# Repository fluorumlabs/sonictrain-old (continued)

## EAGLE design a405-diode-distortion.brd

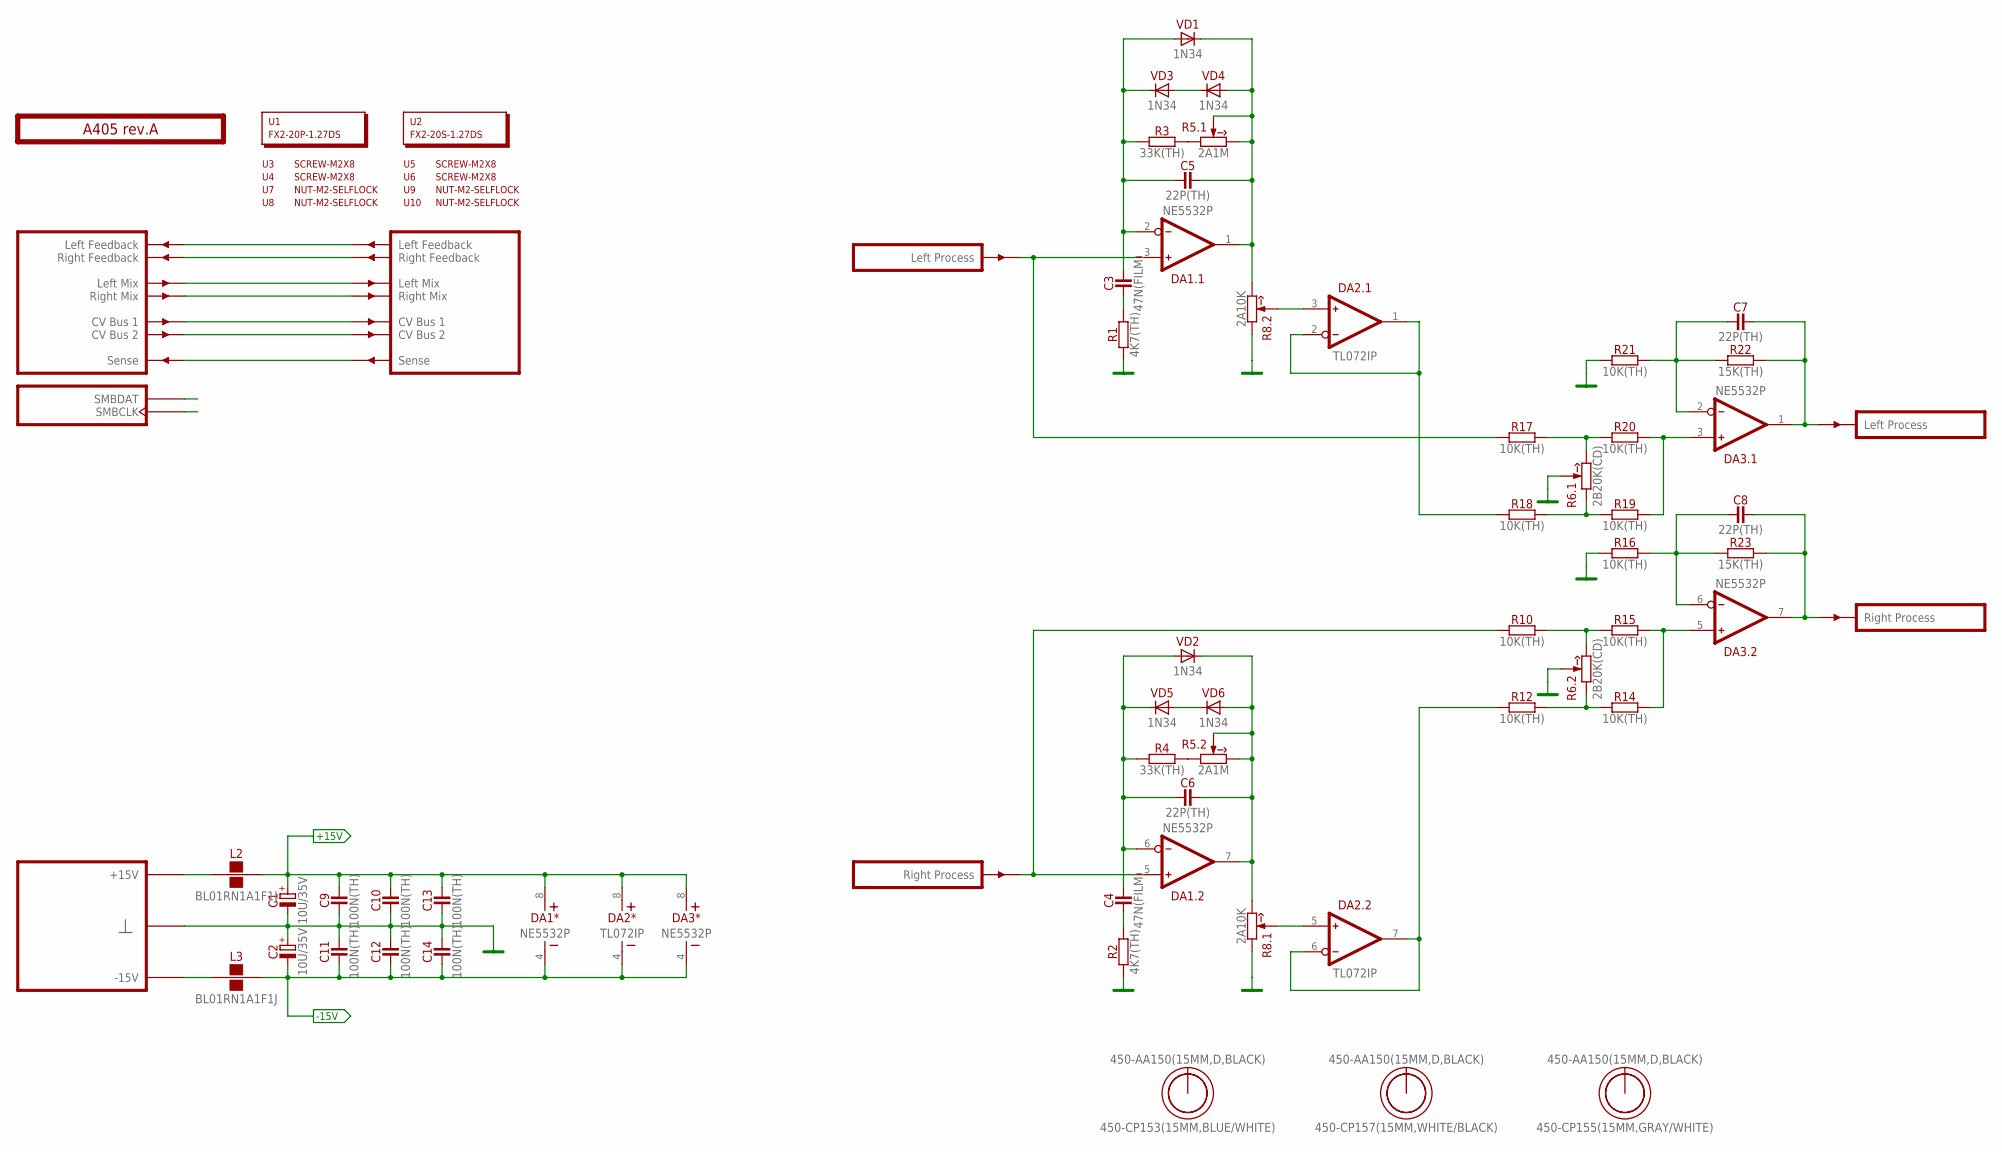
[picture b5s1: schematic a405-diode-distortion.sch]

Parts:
C1, C2: 10U/35V; E2-5
C3, C4: 47N(FILM); C050-025X075
C5, C6, C7, C8: 22P(TH); C050-024X044
C9, C10, C11, C12, C13, C14: 100N(TH); C050-024X044
DA1, DA3: NE5532P; DIP-8
DA2: TL072IP; DIP-8
L2, L3: BL01RN1A1F1J; BL01RN1A
O2, O3, O4: 450-AA150(15MM,D,BLACK); EMPTY
O5: 450-CP155(15MM,GRAY/WHITE); EMPTY
O6: 450-CP157(15MM,WHITE/BLACK); EMPTY
O7: 450-CP153(15MM,BLUE/WHITE); EMPTY
PCB1: A405 rev.A; ST2-BOARD-50
R1, R2: 4K7(TH); R-0207/10
R3, R4: 33K(TH); R-0207/10
R5: 2A1M; RV11-DUAL
R6: 2B20K(CD); RV11-DUAL
R8: 2A10K; RV11-DUAL
R10, R12, R14, R15, R16, R17, R18, R19, R20, R21: 10K(TH); R-0207/10
R22, R23: 15K(TH); R-0207/10
U1: FX2-20P-1.27DS; EMPTY
U2: FX2-20S-1.27DS; EMPTY
U3, U4, U5, U6: SCREW-M2X8; EMPTY
U7, U8, U9, U10: NUT-M2-SELFLOCK; EMPTY
VD1, VD2, VD3, VD4, VD5, VD6: 1N34; DO35-15

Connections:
+15V: C1.+, C9.2, C10.2, C13.2, DA1.8 (V+), DA2.8 (V+), DA3.8 (V+), L2.2
-15V: C2.-, C11.1, C12.1, C14.1, DA1.4 (V-), DA2.4 (V-), DA3.4 (V-), L3.2
FBK_LEFT: PCB1.ALFBK (LFBK), PCB1.ALFBK' (LFBK')
FBK_RIGHT: PCB1.ARFBK (RFBK), PCB1.ARFBK' (RFBK')
GND: C1.-, C2.+, C9.1, C10.1, C11.2, C12.2, C13.1, C14.2, PCB1.B4 (GND), PCB1.B4' (GND), PCB1.B5 (GND), PCB1.B5' (GND), PCB1.B6 (GND), PCB1.B6' (GND), PCB1.B7 (GND), PCB1.B7' (GND), PCB1.B8 (GND), PCB1.B8' (GND), R1.1, R2.1, R6.2 (W), R6.2' (W), R8.1 (CCW), R8.1' (CCW), R16.1, R21.1
LMIX: PCB1.ALMIX (LMIX), PCB1.ALMIX' (LMIX')
unnamed: R3.2, R5.1 (CCW)
unnamed: R4.2, R5.1' (CCW)
unnamed: C7.2, DA3.1 (OUT), PCB1.BOUTL' (OUTL), R22.2
unnamed: C3.1, R1.2
unnamed: R6.3 (CW), R17.2, R20.1
unnamed: DA1.5 (IN+), PCB1.BINR (INR), R10.1
unnamed: C6.2, DA1.7 (OUT), R5.2' (W), R5.3' (CW), R8.3 (CW), VD2.C, VD6.A
unnamed: C4.1, R2.2
unnamed: C5.2, DA1.1 (OUT), R5.2 (W), R5.3 (CW), R8.3' (CW), VD1.C, VD4.A
unnamed: C4.2, C6.1, DA1.6 (IN-), R4.1, VD2.A, VD5.C
unnamed: C8.1, DA3.6 (IN-), R16.2, R23.1
unnamed: DA3.5 (IN+), R14.2, R15.2
unnamed: DA3.3 (IN+), R19.2, R20.2
unnamed: VD3.A, VD4.C
unnamed: R6.1' (CCW), R12.2, R14.1
unnamed: PCB1.BSENSE (SENSE), PCB1.BSENSE' (SENSE')
unnamed: C3.2, C5.1, DA1.2 (IN-), R3.1, VD1.A, VD3.C
unnamed: DA1.3 (IN+), PCB1.BINL (INL), R17.1
unnamed: C8.2, DA3.7 (OUT), PCB1.BOUTR' (OUTR), R23.2
unnamed: VD5.A, VD6.C
unnamed: DA2.5 (IN+), R8.2 (W)
unnamed: DA2.6 (IN-), DA2.7 (OUT), R12.1
unnamed: DA2.3 (IN+), R8.2' (W)
unnamed: DA2.1 (OUT), DA2.2 (IN-), R18.1
unnamed: L3.1, PCB1.A-15 (P-15V), PCB1.A-15' (P-15V), PCB1.B-15 (P-15V), PCB1.B-15' (P-15V)
unnamed: PCB1.ASMBDAT (SMBDAT), PCB1.ASMBDAT' (SMBDAT)
unnamed: PCB1.ACV1 (CV1), PCB1.ACV1' (CV1')
unnamed: PCB1.ACV2 (CV2), PCB1.ACV2' (CV2')
unnamed: PCB1.ASMBCLK (SMBCLK), PCB1.ASMBCLK' (SMBCLK)
unnamed: R6.1 (CCW), R18.2, R19.1
unnamed: R6.3' (CW), R10.2, R15.1
unnamed: C7.1, DA3.2 (IN-), R21.2, R22.1
P+15V: L2.1, PCB1.A+15 (P+15V), PCB1.A+15' (P+15V), PCB1.B+15 (P+15V), PCB1.B+15' (P+15V)
RMIX: PCB1.ARMIX (RMIX), PCB1.ARMIX' (RMIX')

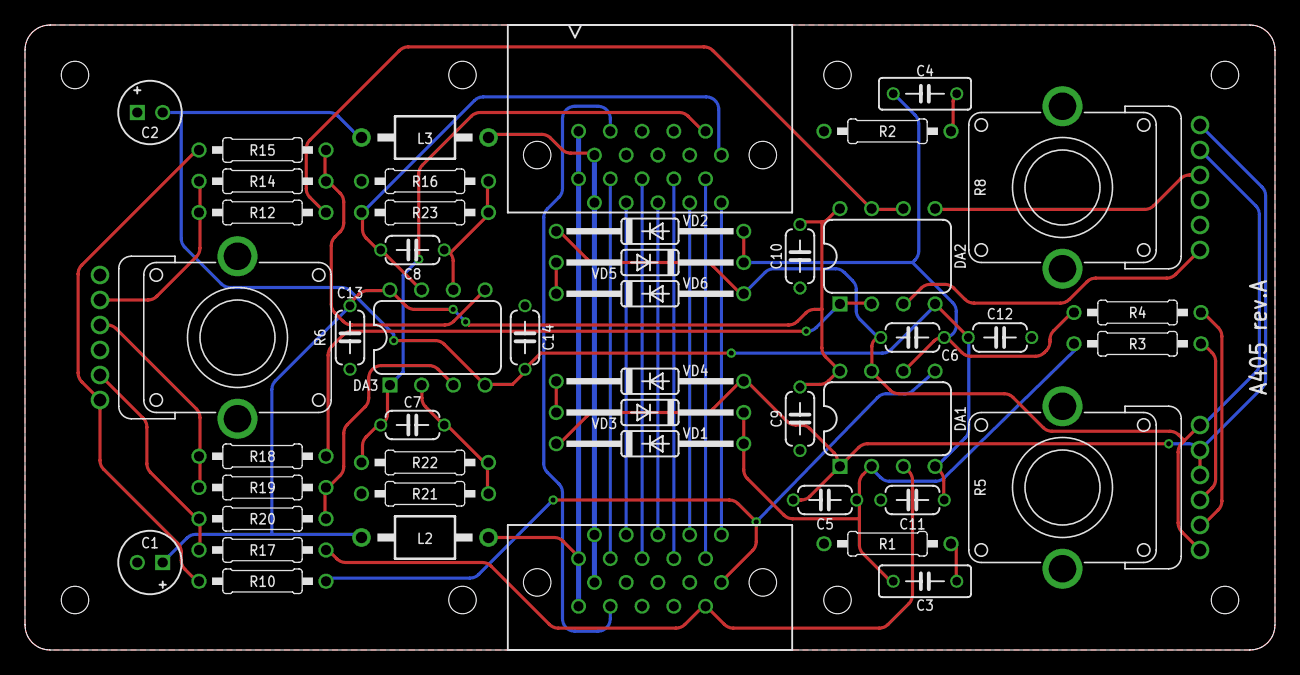
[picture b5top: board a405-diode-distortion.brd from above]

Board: 2 copper layers, 100.0 x 50.0 mm, 61 parts (0 on the bottom side), 40 nets.

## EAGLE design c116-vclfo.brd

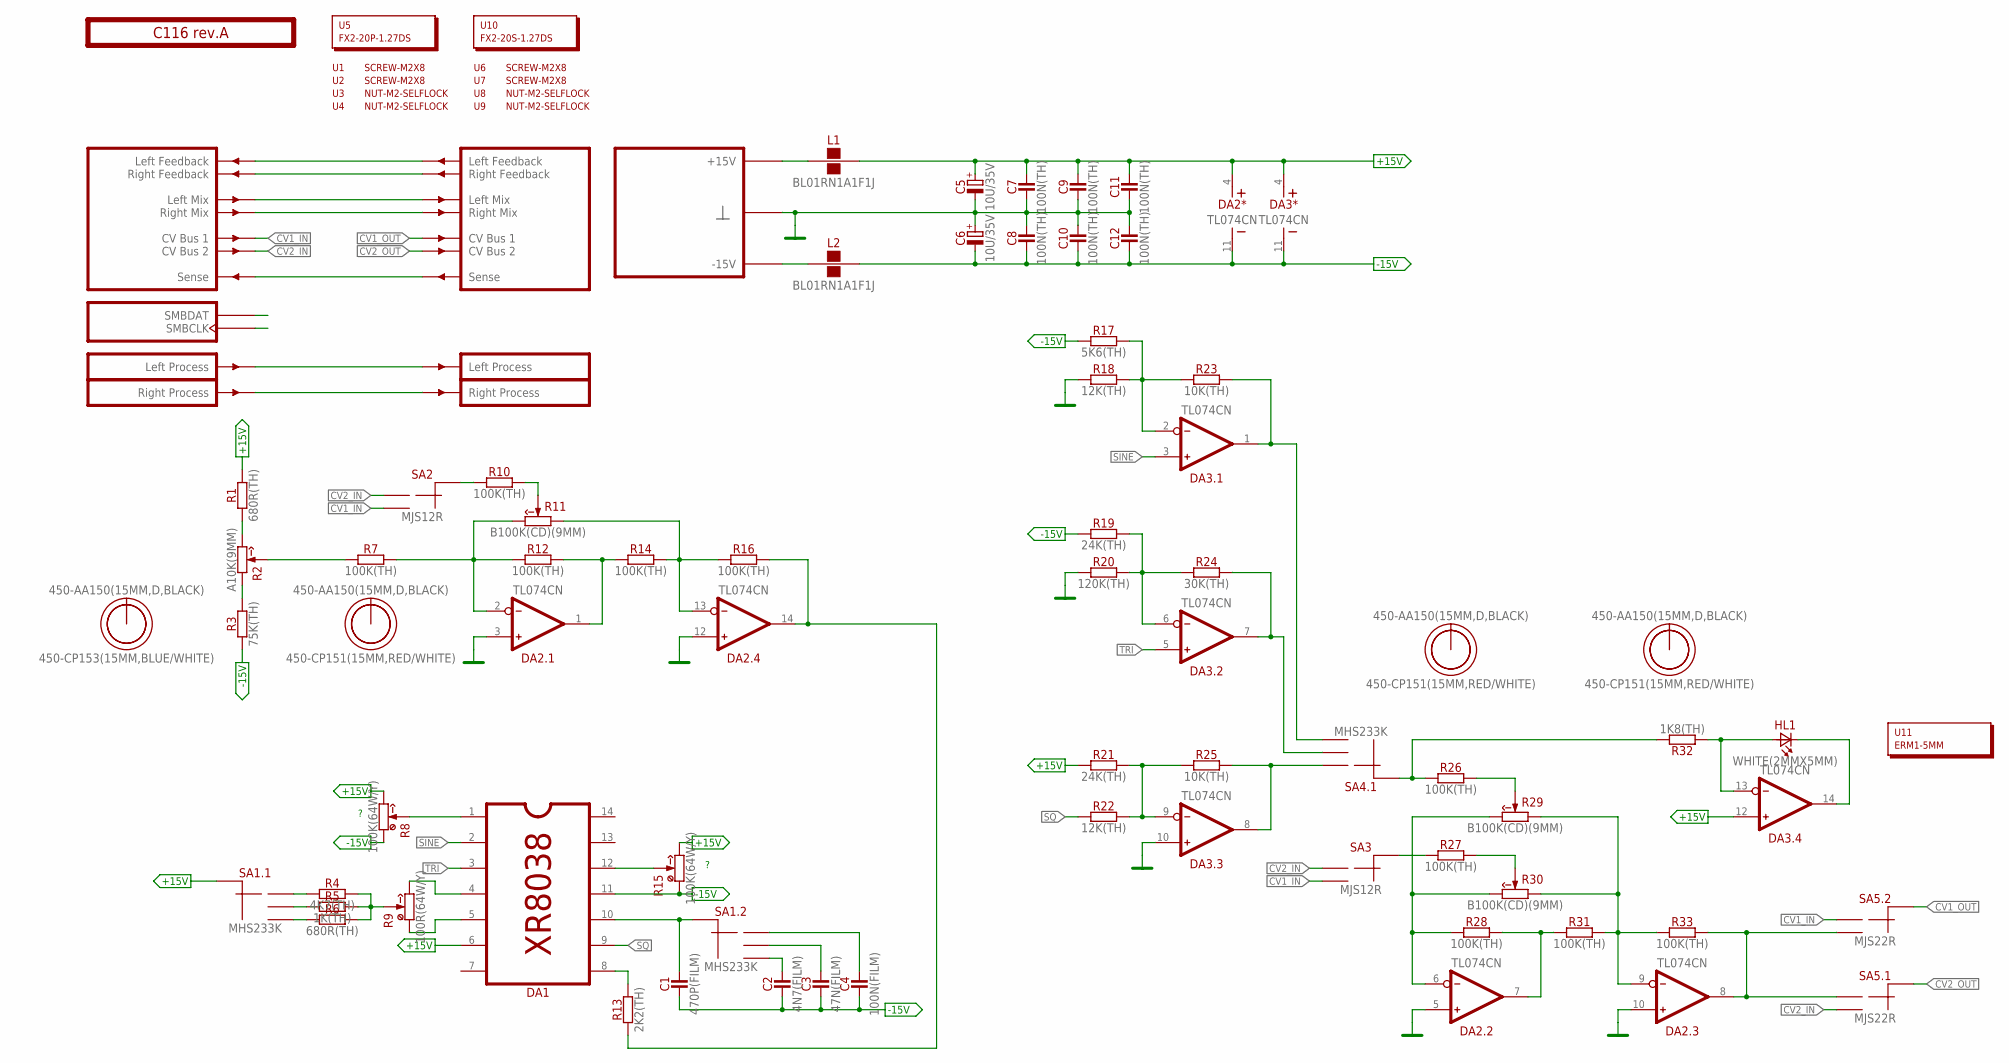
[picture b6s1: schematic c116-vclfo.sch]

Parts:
C1: 470P(FILM); C050-055X075
C2: 4N7(FILM); C050-025X075
C3: 47N(FILM); C050-025X075
C4: 100N(FILM); C050-025X075
C5, C6: 10U/35V; E2-5
C7, C8, C9, C10, C11, C12: 100N(TH); C050-024X044
DA1: XR8038; DIP-14
DA2, DA3: TL074CN; DIP-14
HL1: WHITE(2MMX5MM); LED2X5
L1, L2: BL01RN1A1F1J; BL01RN1A
O1, O3, O5, O7: 450-AA150(15MM,D,BLACK); EMPTY
O2: 450-CP153(15MM,BLUE/WHITE); EMPTY
O4, O6, O8: 450-CP151(15MM,RED/WHITE); EMPTY
PCB1: C116 rev.A; ST2-BOARD-74
R1, R6: 680R(TH); R-0207/10
R2: A10K(9MM); RV09-SINGLE
R3: 75K(TH); R-0207/10
R4: 4K7(TH); R-0207/10
R5: 1K(TH); R-0207/10
R7, R10, R12, R14, R16, R26, R27, R28, R31, R33: 100K(TH); R-0207/10
R8, R15: 100K(64W/Y); 64W
R9: 100R(64W/Y); 64W
R11, R29, R30: B100K(CD)(9MM); RV09-SINGLE
R13: 2K2(TH); R-0207/10
R17: 5K6(TH); R-0207/10
R18, R22: 12K(TH); R-0207/10
R19, R21: 24K(TH); R-0207/10
R20: 120K(TH); R-0207/10
R23, R25: 10K(TH); R-0207/10
R24: 30K(TH); R-0207/10
R32: 1K8(TH); R-0207/10
SA1, SA4: MHS233K; APEM-MHS233K
SA2, SA3: MJS12R; APEM-MJS12R
SA5: MJS22R; APEM-MJS22R
U1, U2, U6, U7: SCREW-M2X8; EMPTY
U3, U4, U8, U9: NUT-M2-SELFLOCK; EMPTY
U5: FX2-20P-1.27DS; EMPTY
U10: FX2-20S-1.27DS; EMPTY
U11: ERM1-5MM; EMPTY

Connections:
+15V: C5.+, C7.2, C9.2, C11.2, DA1.6, DA2.4 (V+), DA3.4 (V+), DA3.12 (IN+), L1.2, R1.2, R8.3 (CW), R15.3 (CW), R21.1, SA1.CMN (CM)
-15V: C1.1, C2.1, C3.1, C4.1, C6.-, C8.1, C10.1, C12.1, DA1.11, DA2.11 (V-), DA3.11 (V-), L2.2, R3.1, R8.1 (CCW), R15.1 (CCW), R17.1, R19.1
CV1_IN: PCB1.ACV1 (CV1), SA2.NO (2), SA3.NO (2), SA5.NC2 (1)
CV1_OUT: PCB1.ACV1' (CV1'), SA5.C2 (CM)
CV2_IN: PCB1.ACV2 (CV2), SA2.NC (1), SA3.NC (1), SA5.NO1 (2)
CV2_OUT: PCB1.ACV2' (CV2'), SA5.C1 (CM)
GND: C5.-, C6.+, C7.1, C8.2, C9.1, C10.2, C11.1, C12.2, DA2.3 (IN+), DA2.5 (IN+), DA2.10 (IN+), DA2.12 (IN+), DA3.10 (IN+), PCB1.B4 (GND), PCB1.B4' (GND), PCB1.B5 (GND), PCB1.B5' (GND), PCB1.B6 (GND), PCB1.B6' (GND), PCB1.B7 (GND), PCB1.B7' (GND), PCB1.B8 (GND), PCB1.B8' (GND), R18.1, R20.1
LMIX: PCB1.ALMIX (LMIX), PCB1.ALMIX' (LMIX')
unnamed: L1.1, PCB1.A+15 (P+15V), PCB1.A+15' (P+15V), PCB1.B+15 (P+15V), PCB1.B+15' (P+15V)
unnamed: PCB1.ALFBK (LFBK), PCB1.ALFBK' (LFBK')
unnamed: R10.2, R11.2 (W)
unnamed: PCB1.ARFBK (RFBK), PCB1.ARFBK' (RFBK')
unnamed: DA2.2 (IN-), R7.2, R11.3 (CW), R12.1
unnamed: DA2.1 (OUT), R12.2, R14.1
unnamed: DA2.13 (IN-), R11.1 (CCW), R14.2, R16.1
unnamed: DA2.14 (OUT), R13.1, R16.2
unnamed: R10.1, SA2.C (CM)
unnamed: PCB1.BINL (INL), PCB1.BOUTL' (OUTL)
unnamed: PCB1.BINR (INR), PCB1.BOUTR' (OUTR)
unnamed: R2.2 (W), R7.1
unnamed: R1.1, R2.3 (CW)
unnamed: R2.1 (CCW), R3.2
unnamed: DA1.4, R9.3 (CW)
unnamed: PCB1.BSENSE (SENSE), PCB1.BSENSE' (SENSE')
unnamed: DA1.5, R9.1 (CCW)
unnamed: R4.2, R5.2, R6.2, R9.S (W), R9.S@1 (W)
unnamed: R4.1, SA1.1
unnamed: R5.1, SA1.2
unnamed: R6.1, SA1.3
unnamed: DA3.8 (OUT), R25.2, SA4.1
unnamed: C2.2, SA1.3' (3)
unnamed: C3.2, SA1.2' (2)
unnamed: L2.1, PCB1.A-15 (P-15V), PCB1.A-15' (P-15V), PCB1.B-15 (P-15V), PCB1.B-15' (P-15V)
unnamed: C4.2, SA1.1' (1)
unnamed: C1.2, DA1.10, SA1.CMN' (CM)
unnamed: DA1.8, R13.2
unnamed: DA3.7 (OUT), R24.2, SA4.2
unnamed: DA1.12, R15.S (W), R15.S@1 (W)
unnamed: DA1.1, R8.S (W), R8.S@1 (W)
unnamed: DA3.1 (OUT), R23.2, SA4.3
unnamed: DA3.2 (IN-), R17.2, R18.2, R23.1
unnamed: DA3.6 (IN-), R19.2, R20.2, R24.1
unnamed: DA3.9 (IN-), R21.2, R22.2, R25.1
unnamed: DA3.13 (IN-), HL1.A, R32.1
unnamed: R27.2, R30.2 (W)
unnamed: PCB1.ASMBDAT (SMBDAT), PCB1.ASMBDAT' (SMBDAT)
unnamed: DA3.14 (OUT), HL1.K (C)
unnamed: DA2.6 (IN-), R28.1, R29.3 (CW), R30.3 (CW)
unnamed: PCB1.ASMBCLK (SMBCLK), PCB1.ASMBCLK' (SMBCLK)
unnamed: DA2.7 (OUT), R28.2, R31.1
unnamed: DA2.9 (IN-), R29.1 (CCW), R30.1 (CCW), R31.2, R33.1
unnamed: DA2.8 (OUT), R33.2, SA5.NC1 (1), SA5.NO2 (2)
unnamed: R27.1, SA3.C (CM)
unnamed: R26.2, R29.2 (W)
unnamed: R26.1, R32.2, SA4.CMN (CM)
RMIX: PCB1.ARMIX (RMIX), PCB1.ARMIX' (RMIX')
SINE: DA1.2, DA3.3 (IN+)
SQ: DA1.9, R22.1
TRI: DA1.3, DA3.5 (IN+)

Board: 2 copper layers, 76 parts (0 on the bottom side), 59 nets, no tracks yet.
